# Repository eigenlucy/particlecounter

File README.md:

# particlecounter

Alpha particle detector based on the CERN Open Source Particle Counter build

Created by lucy moglia <eigenlucy@proton.me>

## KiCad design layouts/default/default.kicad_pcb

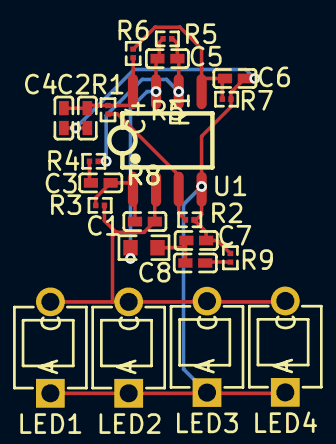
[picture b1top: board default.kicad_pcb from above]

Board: 2 copper layers, 22 parts (0 on the bottom side), 11 nets.

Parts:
C1, C2, C3, C4, C5, C6, C7, C8: 100nF ±10% 16V X7R; C0402-b3ef17
LED1, LED2, LED3, LED4: SENSOR-TH_BPW34-c0a4b0
R1, R2, R3, R4, R5, R6, R7, R9: 0Ω 50mW; R0201-27027e
R8: 10kΩ ±1% 100mW; R0603-ebcab9
U1: SOIC-8_L5.0-W4.0-P1.27-LS6.0-BL-294f77

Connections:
IN1plus: R1.2, R2.1, U1.3
IN2minus: C5.1, R4.2, R5.1, U1.6
IN2plus: C6.1, R6.2, R7.1, U1.5
K: C1.1, LED1.2, LED2.2, LED3.2, LED4.2, R3.1, U1.2
OUT1: C1.2, C3.1, R3.2, U1.1
OUT2: C5.2, R5.2, R8.1, U1.7
VCC: C2.1, C4.1, R1.1, R6.1, U1.8
gnd: C2.2, C4.2, C6.2, C7.2, LED1.1, LED2.1, LED3.1, LED4.1, R2.2, R7.2, R9.2, U1.4
net: C7.1, C8.1, R8.2
net-1: C3.2, R4.1
out: C8.2, R9.1

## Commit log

2025-04-23 V1, added pubishing info
